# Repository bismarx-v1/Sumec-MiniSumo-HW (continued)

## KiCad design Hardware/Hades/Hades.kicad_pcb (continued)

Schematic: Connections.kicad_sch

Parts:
C68, C69, C70, C71: 100n; C_0402_1005Metric
D2, D3, D4, D5: SD103AWS; D_SOD-323
FB3, FB4, FB5, FB6: Ferrite_Bead_Small; L_0402_1005Metric
GPS_BAT1: Conn_01x02; Molex_PicoBlade_53048-0210_1x02_P1.25mm_Horizontal
JP1, JP2: SolderJumper_2_Open; SolderJumper-2_P1.3mm_Open_RoundedPad1.0x1.5mm
JP4: Jumper_3_Open; SolderJumper-3_P1.3mm_Open_RoundedPad1.0x1.5mm
LED13, LED14: G; LED_0603_1608Metric
R40, R41, R42, R43, R44, R45, R46, R47, R48, R49: 10; R_0402_1005Metric
R50, R51: 0; R_0603_1608Metric
R52, R53, R55, R56: 22; R_0402_1005Metric
R54, R57: 560; R_0402_1005Metric
R58, R59: 560; R_0603_1608Metric
SWD1, SWD2: Conn_02x05_Odd_Even; PinHeader_2x05_P1.27mm_Vertical_SMD
U11, U12: otter:CH330; SSOP-8_3.9x5.05mm_P1.27mm
USB1, USB2, USB3, USB4: USB_B_Micro; USB_Micro-B_Wuerth_629105150521_CircularHoles

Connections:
+3V3: JP4.1 (A), SWD1.1, SWD2.1; also elsewhere on the board
+5V: FB3.1, FB4.1, FB5.1, FB6.1; also elsewhere on the board
GND: C68.1, C69.1, C70.1, C71.1, GPS_BAT1.2, R58.1, R59.1, SWD1.3, SWD1.5, SWD1.9, SWD2.3, SWD2.5, SWD2.9, U11.3, U12.3, USB1.5 (GND), USB1.6 (Shield), USB2.5 (GND), USB2.6 (Shield), USB3.5 (GND), USB3.6 (Shield), USB4.5 (GND), USB4.6 (Shield); also elsewhere on the board
GPIO_A_FCC: R40.2; also elsewhere on the board
GPIO_A_NAVC: R40.1; also elsewhere on the board
GPIO_B_FCC: R41.2; also elsewhere on the board
GPIO_B_NAVC: R41.1; also elsewhere on the board
GPIO_C_FCC: R42.2; also elsewhere on the board
GPIO_C_NAVC: R42.1; also elsewhere on the board
GPIO_D_FCC: R43.2; also elsewhere on the board
GPIO_D_NAVC: R43.1; also elsewhere on the board
GPIO_E_FCC: R44.2; also elsewhere on the board
GPIO_E_NAVC: R44.1; also elsewhere on the board
GPIO_F_FCC: R45.2; also elsewhere on the board
GPIO_F_NAVC: R45.1; also elsewhere on the board
GPIO_G_FCC: R46.2; also elsewhere on the board
GPIO_G_NAVC: R46.1; also elsewhere on the board
GPIO_H_FCC: R47.2; also elsewhere on the board
GPIO_H_NAVC: R47.1; also elsewhere on the board
GPS_BAT_BACKUP: JP4.2 (C); also elsewhere on the board
I2C1_SCL_FCC: R50.2; also elsewhere on the board
I2C1_SDA_FCC: R51.2; also elsewhere on the board
I2C2_SCL_NAVC: R50.1; also elsewhere on the board
I2C2_SDA_NAVC: R51.1; also elsewhere on the board
unnamed: C68.2, D4.2 (A), LED13.2 (A), U11.5, USB3.1 (VBUS)
unnamed: C69.2, U11.8
unnamed: C70.2, D5.2 (A), LED14.2 (A), U12.5, USB4.1 (VBUS)
unnamed: C71.2, U12.8
unnamed: D2.1 (K), FB3.2
unnamed: D2.2 (A), JP1.1 (A), USB1.1 (VBUS)
unnamed: D3.1 (K), FB4.2
unnamed: D3.2 (A), JP2.1 (A), USB2.1 (VBUS)
unnamed: D4.1 (K), FB5.2
unnamed: D5.1 (K), FB6.2
unnamed 119: GPS_BAT1.1, JP4.3 (B); also elsewhere on the board
unnamed: LED13.1 (K), R58.2
unnamed: LED14.1 (K), R59.2
unnamed: R52.2, USB1.3 (D+)
unnamed: R53.2, USB1.2 (D-)
unnamed: R54.2, USB1.4 (ID)
unnamed: R55.2, USB2.3 (D+)
unnamed: R56.2, USB2.2 (D-)
unnamed: R57.2, USB2.4 (ID)
unnamed: U11.1, USB3.3 (D+)
unnamed: U11.2, USB3.2 (D-)
unnamed: U12.1, USB4.3 (D+)
unnamed: U12.2, USB4.2 (D-)
UART1_RX_FCC: U11.6; also elsewhere on the board
UART1_TX_FCC: U11.7; also elsewhere on the board
UART2_RX_FCC: R48.2; also elsewhere on the board
UART2_RX_NAVC: R49.1; also elsewhere on the board
UART2_TX_FCC: R49.2; also elsewhere on the board
UART2_TX_NAVC: R48.1; also elsewhere on the board
UART3_RX_NAVC: U12.6; also elsewhere on the board
UART3_TX_NAVC: U12.7; also elsewhere on the board
USB_DM_FCC: R53.1; also elsewhere on the board
USB_DM_NAVC: R56.1; also elsewhere on the board
USB_DP_FCC: R52.1; also elsewhere on the board
USB_DP_NAVC: R55.1; also elsewhere on the board
USB_ID_FCC: R54.1; also elsewhere on the board
USB_ID_NAVC: R57.1; also elsewhere on the board
USB_VBUS_FCC: JP1.2 (B); also elsewhere on the board
USB_VBUS_NAVC: JP2.2 (B); also elsewhere on the board

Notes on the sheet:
GPS Backup Battery
UART Connections
Connections (FCC <-> NAVC)
USB Debug
I2C Connections
Connector: M50-3600542R
Serial Wire Debug
CH330 UART to USB Converters
USB Programming
GPIO Connections
Connectors (Programming & Debug)
GPS Backup Battery Jumper and Connector

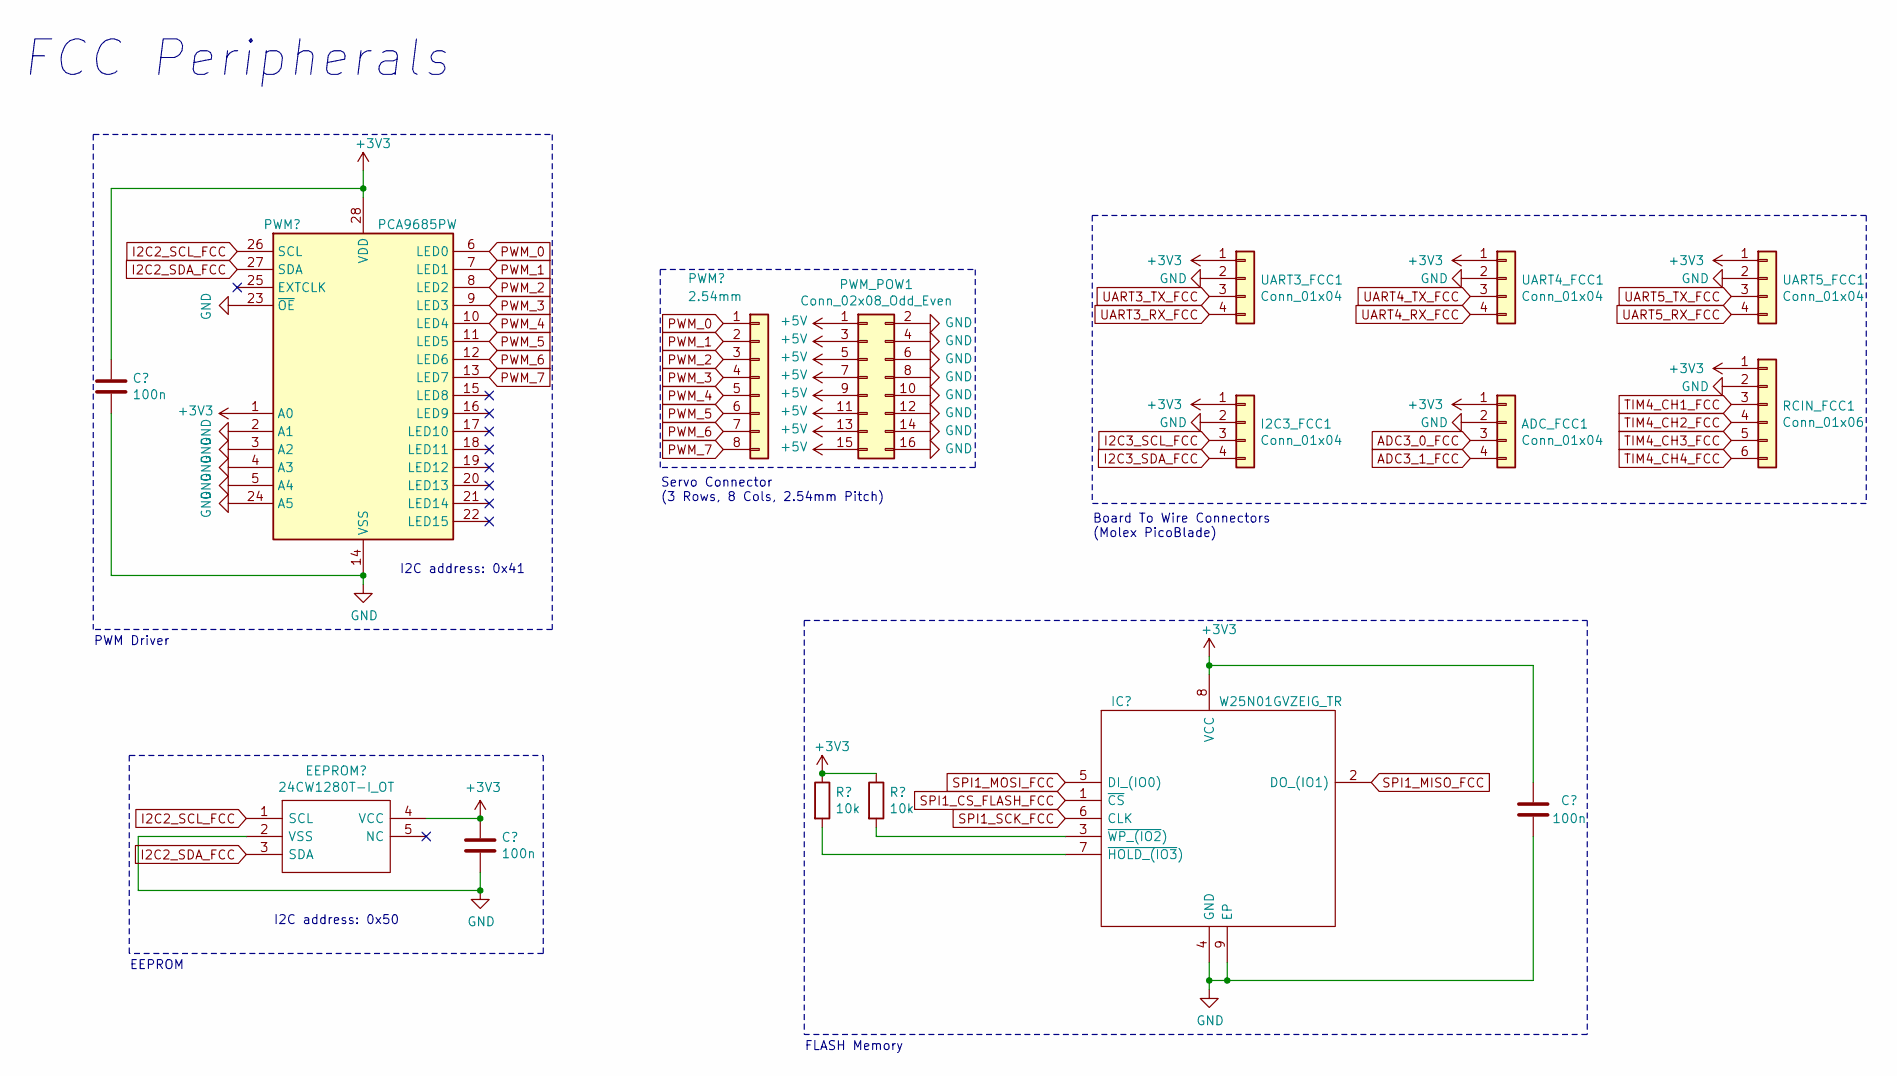
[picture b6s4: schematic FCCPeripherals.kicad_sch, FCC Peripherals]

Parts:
ADC_FCC1: Conn_01x04; Molex_PicoBlade_53048-0410_1x04_P1.25mm_Horizontal
C34, C35, C36: 100n; C_0402_1005Metric
I2C3_FCC1: Conn_01x04; Molex_PicoBlade_53048-0410_1x04_P1.25mm_Horizontal
PWM_POW1: Conn_02x08_Odd_Even; PinHeader_2x08_P2.54mm_Vertical
PWM_SIG1: 2.54mm; PinHeader_1x08_P2.54mm_Vertical
R24, R25: 10k; R_0402_1005Metric
RCIN_FCC1: Conn_01x06; Molex_PicoBlade_53048-0610_1x06_P1.25mm_Horizontal
U2: PCA9685PW; TSSOP-28_4.4x9.7mm_P0.65mm
U3: 24CW1280T-I_OT; SOT95P280X145-5N; Manufacturer_Part_Number 24CW1280T-I/OT; Mouser Part Number 579-24CW1280T-I/OT
U4: W25N01GVZEIG_TR; SON127P800X600X80-9N-D; Manufacturer_Part_Number W25N01GVZEIG TR; Mouser Part Number 454-W25N01GVZEIGTR
UART3_FCC1, UART4_FCC1, UART5_FCC1: Conn_01x04; Molex_PicoBlade_53048-0410_1x04_P1.25mm_Horizontal

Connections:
+3V3: ADC_FCC1.1, C34.1, C35.1, C36.2, I2C3_FCC1.1, R24.1, R25.1, RCIN_FCC1.1, U2.1 (A0), U2.28 (VDD), U3.4 (VCC), U4.8 (VCC), UART3_FCC1.1, UART4_FCC1.1, UART5_FCC1.1; also elsewhere on the board
+5V: PWM_POW1.1, PWM_POW1.3, PWM_POW1.5, PWM_POW1.7, PWM_POW1.9, PWM_POW1.11, PWM_POW1.13, PWM_POW1.15; also elsewhere on the board
GND: ADC_FCC1.2, C34.2, C35.2, C36.1, I2C3_FCC1.2, PWM_POW1.2, PWM_POW1.4, PWM_POW1.6, PWM_POW1.8, PWM_POW1.10, PWM_POW1.12, PWM_POW1.14, PWM_POW1.16, RCIN_FCC1.2, U2.2 (A1), U2.3 (A2), U2.4 (A3), U2.5 (A4), U2.14 (VSS), U2.23 (~OE), U2.24 (A5), U3.2 (VSS), U4.4 (GND), U4.9 (EP), UART3_FCC1.2, UART4_FCC1.2, UART5_FCC1.2; also elsewhere on the board
I2C2_SCL_FCC: U2.26 (SCL), U3.1 (SCL); also elsewhere on the board
I2C2_SDA_FCC: U2.27 (SDA), U3.3 (SDA); also elsewhere on the board
unnamed: R24.2, U4.7 (~HOLD_(IO3))
unnamed: R25.2, U4.3 (~WP_(IO2))
PWM_0: PWM_SIG1.1, U2.6 (LED0)
PWM_1: PWM_SIG1.2, U2.7 (LED1)
PWM_2: PWM_SIG1.3, U2.8 (LED2)
PWM_3: PWM_SIG1.4, U2.9 (LED3)
PWM_4: PWM_SIG1.5, U2.10 (LED4)
PWM_5: PWM_SIG1.6, U2.11 (LED5)
PWM_6: PWM_SIG1.7, U2.12 (LED6)
PWM_7: PWM_SIG1.8, U2.13 (LED7)
SPI1_CS_FLASH_FCC: U4.1 (~CS); also elsewhere on the board
SPI1_MISO_FCC: U4.2 (DO_(IO1)); also elsewhere on the board
SPI1_MOSI_FCC: U4.5 (DI_(IO0)); also elsewhere on the board
SPI1_SCK_FCC: U4.6 (CLK); also elsewhere on the board

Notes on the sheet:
I2C address: 0x50
PWM Driver
Servo Connector (3 Rows, 8 Cols, 2.54mm Pitch)
Board To Wire Connectors (Molex PicoBlade)
I2C address: 0x41
FCC Peripherals
EEPROM
FLASH Memory

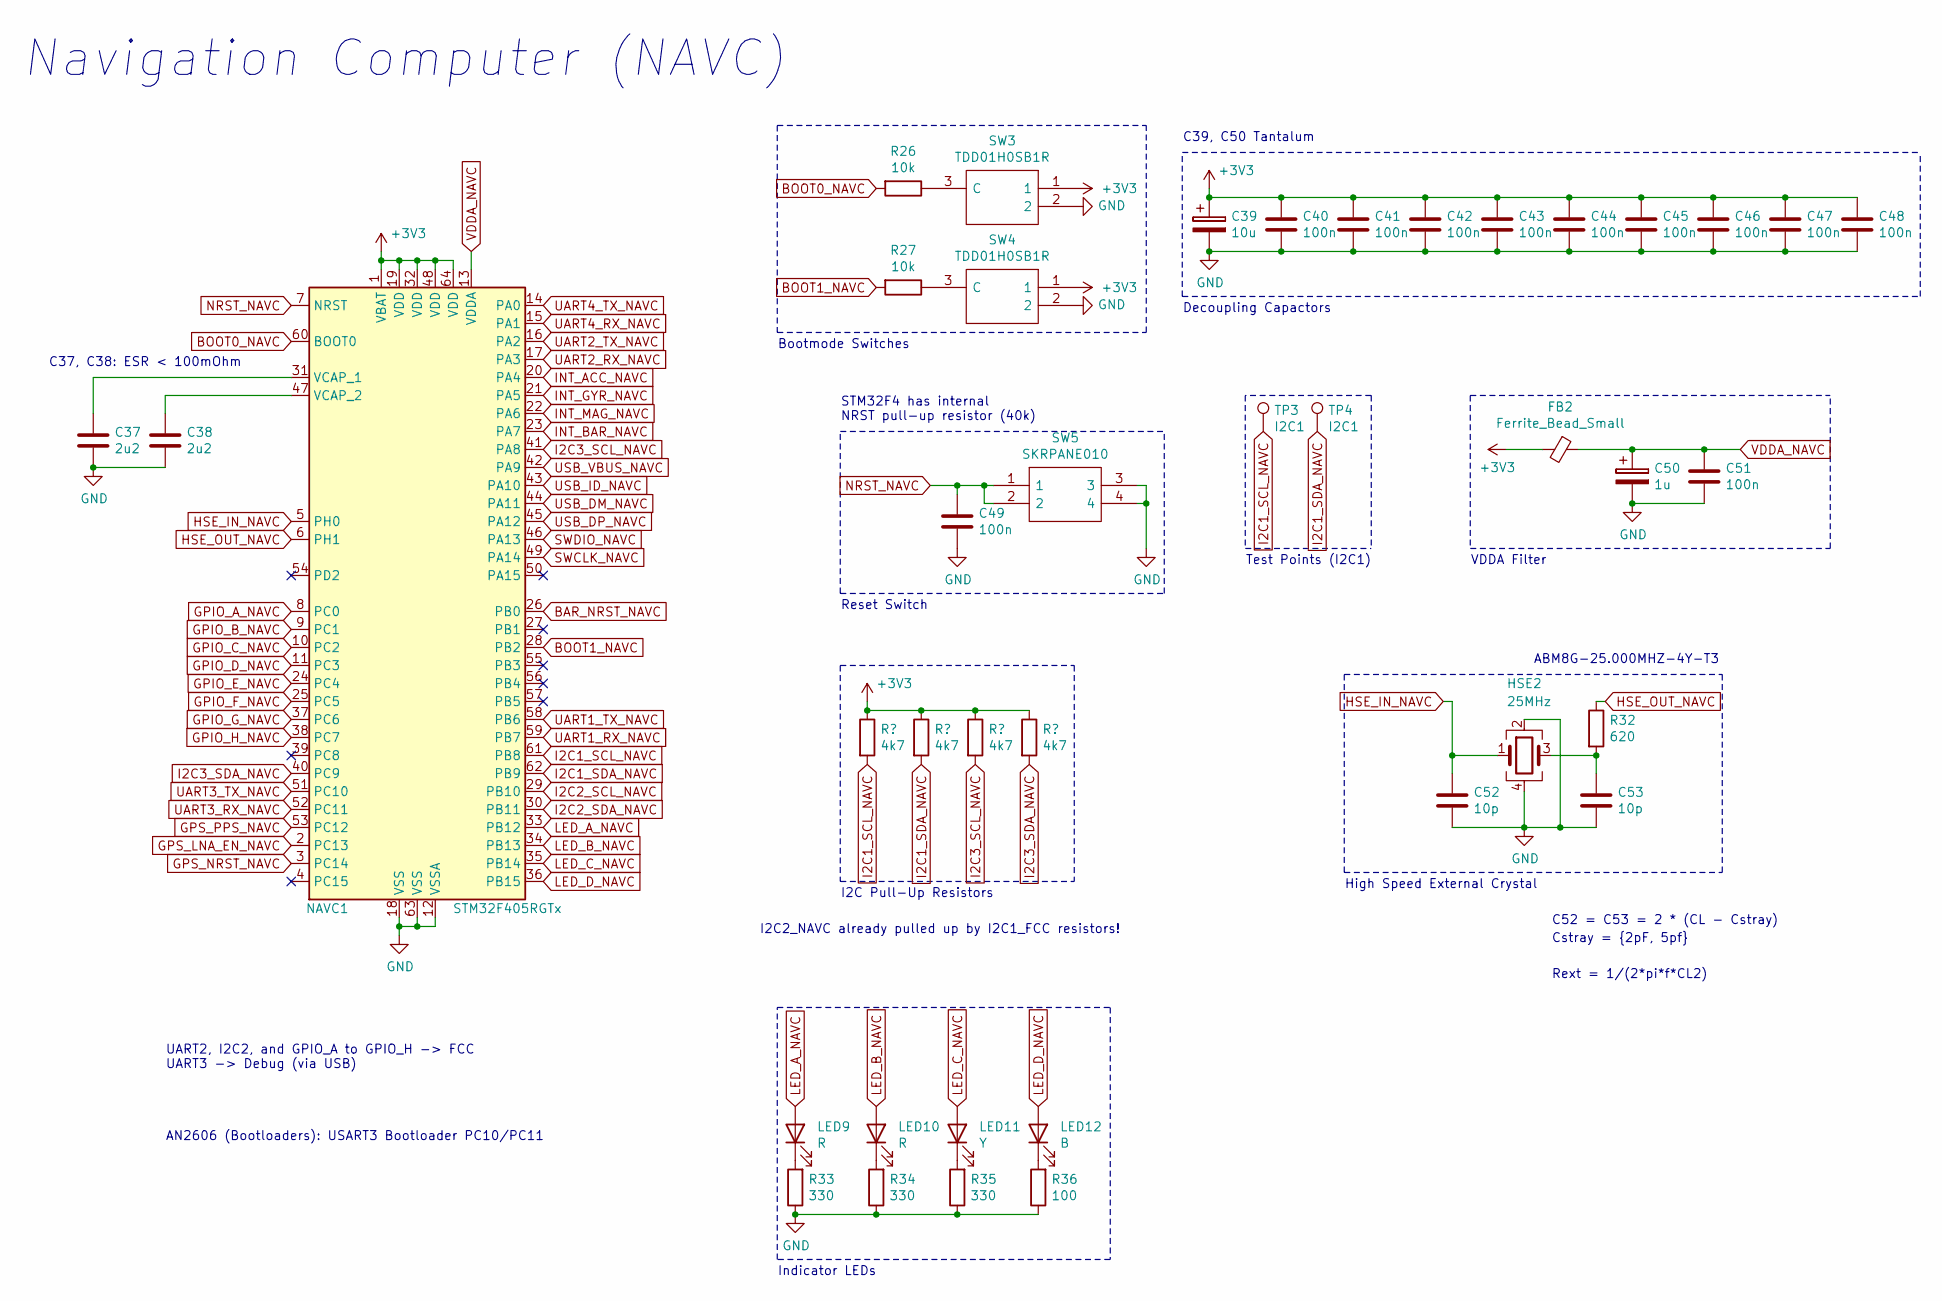
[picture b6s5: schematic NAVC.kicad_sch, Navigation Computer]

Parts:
C37, C38: 2u2; C_0603_1608Metric
C39: 10u; C_0603_1608Metric
C40, C41, C42, C43, C44, C45, C46, C47, C48, C49, C51: 100n; C_0402_1005Metric
C50: 1u; C_0603_1608Metric
C52, C53: 10p; C_0402_1005Metric
FB2: Ferrite_Bead_Small; L_0402_1005Metric
HSE2: 25MHz; Crystal_SMD_Abracon_ABM8G-4Pin_3.2x2.5mm
LED9, LED10: R; LED_0603_1608Metric
LED11: Y; LED_0603_1608Metric
LED12: B; LED_0603_1608Metric
NAVC1: STM32F405RGTx; LQFP-64_10x10mm_P0.5mm
R26, R27: 10k; R_0402_1005Metric
R28, R29, R30, R31: 4k7; R_0402_1005Metric
R32: 620; R_0603_1608Metric
R33, R34, R35: 330; R_0603_1608Metric
R36: 100; R_0603_1608Metric
SW3, SW4: TDD01H0SB1R; SOT175P420X230-3N; Manufacturer_Part_Number TDD01H0SB1R; Mouser Part Number 611-TDD01H0SB1R
SW5: SKRPANE010; SKRPADE010; Manufacturer_Part_Number SKRPANE010; Mouser Part Number 688-SKRPANE010
TP3, TP4: I2C1; TestPoint_Pad_D1.5mm

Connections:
+3V3: C39.1, C40.1, C41.1, C42.1, C43.1, C44.1, C45.1, C46.1, C47.1, C48.1, FB2.2, NAVC1.1 (VBAT), NAVC1.19 (VDD), NAVC1.32 (VDD), NAVC1.48 (VDD), NAVC1.64 (VDD), R28.1, R29.1, R30.1, R31.1, SW3.1, SW4.1; also elsewhere on the board
BOOT0_NAVC: NAVC1.60 (BOOT0), R26.2; also elsewhere on the board
BOOT1_NAVC: NAVC1.28 (PB2), R27.2; also elsewhere on the board
GND: C37.2, C38.2, C39.2, C40.2, C41.2, C42.2, C43.2, C44.2, C45.2, C46.2, C47.2, C48.2, C49.2, C50.2, C51.2, C52.2, C53.2, HSE2.2, HSE2.4, NAVC1.12 (VSSA), NAVC1.18 (VSS), NAVC1.63 (VSS), R33.1, R34.1, R35.1, R36.1, SW3.2, SW4.2, SW5.3, SW5.4; also elsewhere on the board
HSE_IN_NAVC: C52.1, HSE2.1, NAVC1.5 (PH0); also elsewhere on the board
HSE_OUT_NAVC: NAVC1.6 (PH1), R32.1; also elsewhere on the board
I2C1_SCL_NAVC: NAVC1.61 (PB8), R28.2, TP3.1; also elsewhere on the board
I2C1_SDA_NAVC: NAVC1.62 (PB9), R29.2, TP4.1; also elsewhere on the board
I2C3_SCL_NAVC: NAVC1.41 (PA8), R30.2; also elsewhere on the board
I2C3_SDA_NAVC: NAVC1.40 (PC9), R31.2; also elsewhere on the board
LED_A_NAVC: LED9.2 (A), NAVC1.33 (PB12); also elsewhere on the board
LED_B_NAVC: LED10.2 (A), NAVC1.34 (PB13); also elsewhere on the board
LED_C_NAVC: LED11.2 (A), NAVC1.35 (PB14); also elsewhere on the board
LED_D_NAVC: LED12.2 (A), NAVC1.36 (PB15); also elsewhere on the board
NRST_NAVC: C49.1, NAVC1.7 (NRST), SW5.1, SW5.2; also elsewhere on the board
unnamed 68: C37.1, NAVC1.31 (VCAP_1); also elsewhere on the board
unnamed 69: C38.1, NAVC1.47 (VCAP_2); also elsewhere on the board
unnamed: C53.1, HSE2.3, R32.2
unnamed: LED9.1 (K), R33.2
unnamed: LED10.1 (K), R34.2
unnamed: LED11.1 (K), R35.2
unnamed: LED12.1 (K), R36.2
unnamed: R26.1, SW3.3 (C)
unnamed: R27.1, SW4.3 (C)
VDDA_NAVC: C50.1, C51.1, FB2.1, NAVC1.13 (VDDA); also elsewhere on the board

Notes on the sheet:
C39, C50 Tantalum
Decoupling Capactors
I2C2_NAVC already pulled up by I2C1_FCC resistors!
Bootmode Switches
Reset Switch
Test Points (I2C1)
VDDA Filter
I2C Pull-Up Resistors
AN2606 (Bootloaders): USART3 Bootloader PC10/PC11
C37, C38: ESR < 100mOhm
Cstray = {2pF, 5pf}
UART2, I2C2, and GPIO_A to GPIO_H -> FCC UART3 -> Debug (via USB)
ABM8G-25.000MHZ-4Y-T3
High Speed External Crystal
Navigation Computer (NAVC)
Rext = 1/(2*pi*f*CL2)
C52 = C53 = 2 * (CL - Cstray)
Indicator LEDs
STM32F4 has internal NRST pull-up resistor (40k)

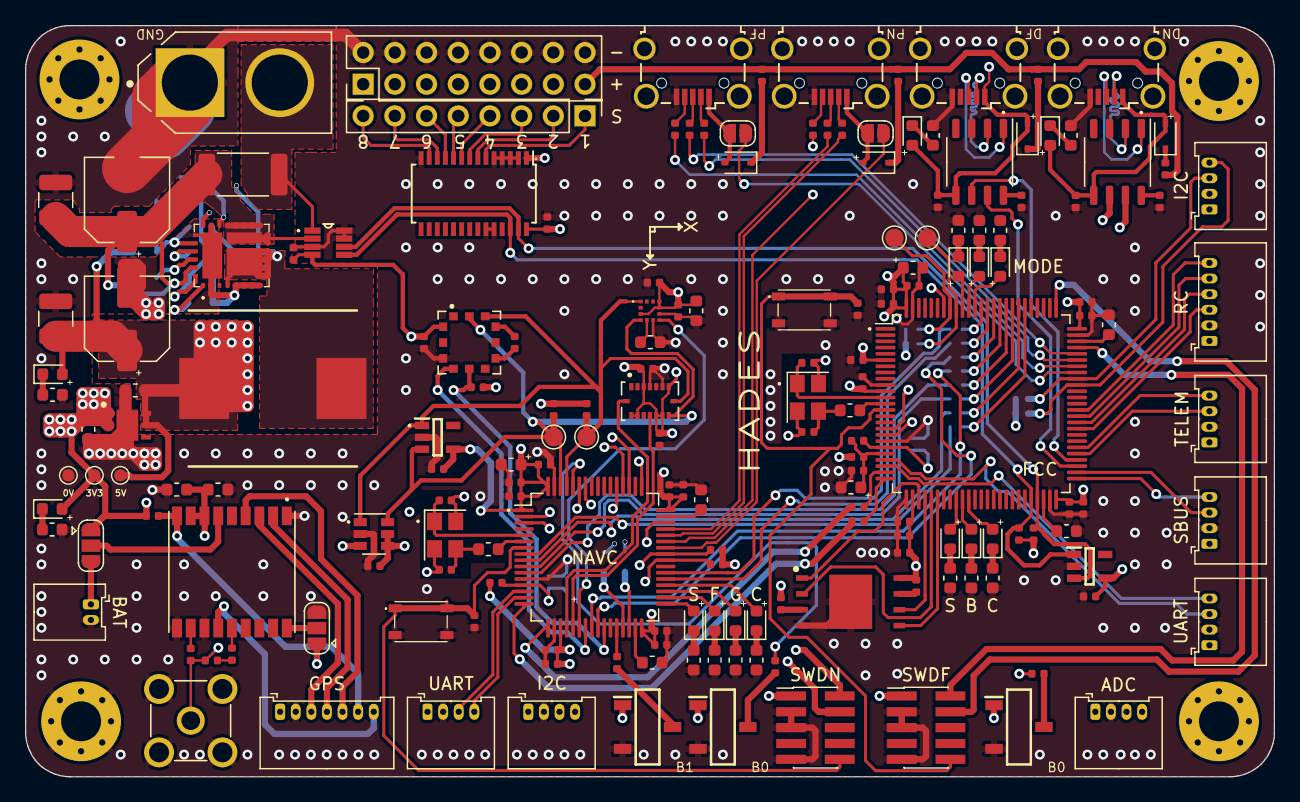
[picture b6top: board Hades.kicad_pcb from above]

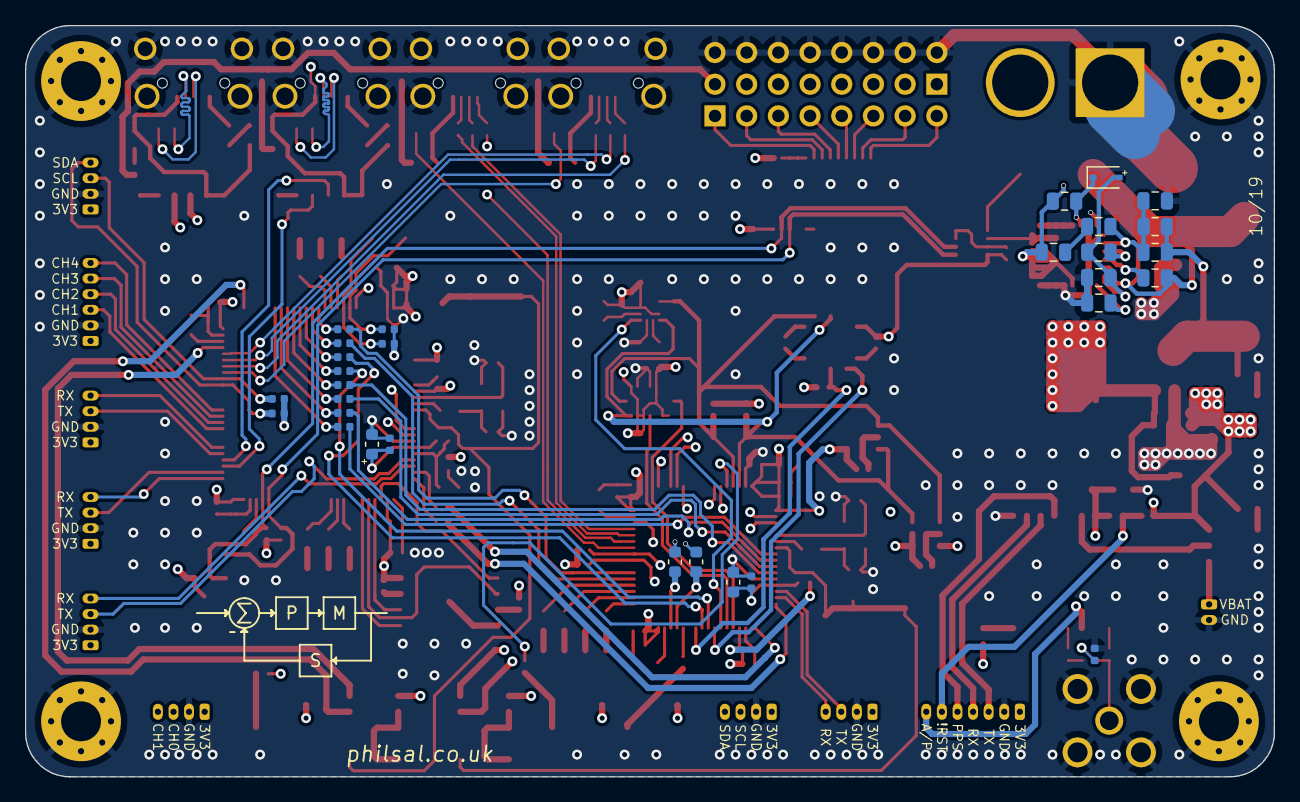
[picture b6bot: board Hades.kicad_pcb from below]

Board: 4 copper layers, 100.1 x 60.2 mm, 211 parts (30 on the bottom side), 174 nets.

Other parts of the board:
5V, 5V#2, 5V#3: TestPoint_Pad_D1.0mm
ADC: Conn_01x04; Molex_PicoBlade_53048-0410_1x04_P1.25mm_Horizontal
BAT: Conn_01x02; Molex_PicoBlade_53048-0210_1x02_P1.25mm_Horizontal
FCC: STM32H753VITx; LQFP-100_14x14mm_P0.5mm
GPS: Conn_01x07; Molex_PicoBlade_53048-0710_1x07_P1.25mm_Horizontal
I2C, I2C#2: Conn_01x04; Molex_PicoBlade_53048-0410_1x04_P1.25mm_Horizontal
NAVC: STM32F405RGTx; LQFP-64_10x10mm_P0.5mm
RC: Conn_01x06; Molex_PicoBlade_53048-0610_1x06_P1.25mm_Horizontal
SBUS: Conn_01x04; Molex_PicoBlade_53048-0410_1x04_P1.25mm_Horizontal
SWDF: Conn_02x05_Odd_Even; PinHeader_2x05_P1.27mm_Vertical_SMD
SWDN: Conn_02x05_Odd_Even; PinHeader_2x05_P1.27mm_Vertical_SMD
TELEM: Conn_01x04; Molex_PicoBlade_53048-0410_1x04_P1.25mm_Horizontal
UART: Conn_01x04; Molex_PicoBlade_53048-0410_1x04_P1.25mm_Horizontal
UART#2: Conn_01x04; Molex_PicoBlade_53048-0410_1x04_P1.25mm_Horizontal

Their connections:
+3V3: 5V#2.1, ADC.1, FCC.6, FCC.11, FCC.27, FCC.50, FCC.75, FCC.100, GPS.1, I2C.1, I2C#2.1, NAVC.1, NAVC.19, NAVC.32, NAVC.48, NAVC.64, RC.1, SBUS.1, SWDF.1, SWDN.1, TELEM.1, UART.1, UART#2.1; also elsewhere on the board
+5V: 5V.1; also elsewhere on the board
ADC3_0_FCC: ADC.3, FCC.17
ADC3_1_FCC: ADC.4, FCC.18
BAR_NRST_NAVC: NAVC.26; also elsewhere on the board
BOOT0_FCC: FCC.94; also elsewhere on the board
BOOT0_NAVC: NAVC.60; also elsewhere on the board
BOOT1_NAVC: NAVC.28; also elsewhere on the board
GND: 5V#3.1, ADC.2, BAT.2, FCC.10, FCC.19, FCC.26, FCC.49, FCC.74, FCC.99, GPS.2, I2C.2, I2C#2.2, NAVC.12, NAVC.18, NAVC.63, RC.2, SBUS.2, SWDF.3, SWDF.5, SWDF.9, SWDN.3, SWDN.5, SWDN.9, TELEM.2, UART.2, UART#2.2; also elsewhere on the board
GPIO_A_FCC: FCC.81; also elsewhere on the board
GPIO_A_NAVC: NAVC.8; also elsewhere on the board
GPIO_B_FCC: FCC.82; also elsewhere on the board
GPIO_B_NAVC: NAVC.9; also elsewhere on the board
GPIO_C_FCC: FCC.83; also elsewhere on the board
GPIO_C_NAVC: NAVC.10; also elsewhere on the board
GPIO_D_FCC: FCC.84; also elsewhere on the board
GPIO_D_NAVC: NAVC.11; also elsewhere on the board
GPIO_E_FCC: FCC.85; also elsewhere on the board
GPIO_E_NAVC: NAVC.24; also elsewhere on the board
GPIO_F_FCC: FCC.86; also elsewhere on the board
GPIO_F_NAVC: NAVC.25; also elsewhere on the board
GPIO_G_FCC: FCC.87; also elsewhere on the board
GPIO_G_NAVC: NAVC.37; also elsewhere on the board
GPIO_H_FCC: FCC.88; also elsewhere on the board
GPIO_H_NAVC: NAVC.38; also elsewhere on the board
GPS_LNA_EN_NAVC: GPS.7, NAVC.2; also elsewhere on the board
GPS_NRST_NAVC: GPS.6, NAVC.3; also elsewhere on the board
GPS_PPS_NAVC: GPS.5, NAVC.53; also elsewhere on the board
HSE_IN_FCC: FCC.12; also elsewhere on the board
HSE_IN_NAVC: NAVC.5; also elsewhere on the board
HSE_OUT_FCC: FCC.13; also elsewhere on the board
HSE_OUT_NAVC: NAVC.6; also elsewhere on the board
I2C1_SCL_FCC: FCC.92; also elsewhere on the board
I2C1_SCL_NAVC: NAVC.61; also elsewhere on the board
I2C1_SDA_FCC: FCC.93; also elsewhere on the board
I2C1_SDA_NAVC: NAVC.62; also elsewhere on the board
I2C2_SCL_FCC: FCC.46; also elsewhere on the board
I2C2_SCL_NAVC: NAVC.29; also elsewhere on the board
I2C2_SDA_FCC: FCC.47; also elsewhere on the board
I2C2_SDA_NAVC: NAVC.30; also elsewhere on the board
I2C3_SCL_FCC: FCC.67, I2C.3; also elsewhere on the board
I2C3_SCL_NAVC: I2C#2.3, NAVC.41; also elsewhere on the board
I2C3_SDA_FCC: FCC.66, I2C.4; also elsewhere on the board
I2C3_SDA_NAVC: I2C#2.4, NAVC.40; also elsewhere on the board
INT_ACC_NAVC: NAVC.20; also elsewhere on the board
INT_BAR_NAVC: NAVC.23; also elsewhere on the board
INT_GYR_NAVC: NAVC.21; also elsewhere on the board
INT_MAG_NAVC: NAVC.22; also elsewhere on the board
LED_A_FCC: FCC.34; also elsewhere on the board
LED_A_NAVC: NAVC.33; also elsewhere on the board
LED_B_FCC: FCC.35; also elsewhere on the board
LED_B_NAVC: NAVC.34; also elsewhere on the board
LED_C_FCC: FCC.36; also elsewhere on the board
LED_C_NAVC: NAVC.35; also elsewhere on the board
LED_D_FCC: FCC.89; also elsewhere on the board
LED_D_NAVC: NAVC.36; also elsewhere on the board
LED_E_FCC: FCC.90; also elsewhere on the board
LED_F_FCC: FCC.91; also elsewhere on the board
NRST_FCC: FCC.14, SWDF.10; also elsewhere on the board
NRST_NAVC: NAVC.7, SWDN.10; also elsewhere on the board
unnamed 65: FCC.48; also elsewhere on the board
unnamed 66: FCC.73; also elsewhere on the board
unnamed 68: NAVC.31; also elsewhere on the board
unnamed 69: NAVC.47; also elsewhere on the board
unnamed 119: BAT.1; also elsewhere on the board
SPI1_CS_FLASH_FCC: FCC.28; also elsewhere on the board
SPI1_MISO_FCC: FCC.30; also elsewhere on the board
SPI1_MOSI_FCC: FCC.31; also elsewhere on the board
SPI1_SCK_FCC: FCC.29; also elsewhere on the board
SWCLK_FCC: FCC.76, SWDF.4
SWCLK_NAVC: NAVC.49, SWDN.4
SWDIO_FCC: FCC.72, SWDF.2
SWDIO_NAVC: NAVC.46, SWDN.2
TIM4_CH1_FCC: FCC.59, RC.3
TIM4_CH2_FCC: FCC.60, RC.4
TIM4_CH3_FCC: FCC.61, RC.5
TIM4_CH4_FCC: FCC.62, RC.6
UART1_RX_FCC: FCC.54; also elsewhere on the board
UART1_RX_NAVC: GPS.4, NAVC.59; also elsewhere on the board
UART1_TX_FCC: FCC.53; also elsewhere on the board
UART1_TX_NAVC: GPS.3, NAVC.58; also elsewhere on the board
UART2_RX_FCC: FCC.25; also elsewhere on the board
UART2_RX_NAVC: NAVC.17; also elsewhere on the board
UART2_TX_FCC: FCC.24; also elsewhere on the board
UART2_TX_NAVC: NAVC.16; also elsewhere on the board
UART3_RX_FCC: FCC.56, TELEM.4
UART3_RX_NAVC: NAVC.52; also elsewhere on the board
UART3_TX_FCC: FCC.55, TELEM.3
UART3_TX_NAVC: NAVC.51; also elsewhere on the board
UART4_RX_FCC: FCC.23, UART#2.4
UART4_RX_NAVC: NAVC.15, UART.4
UART4_TX_FCC: FCC.22, UART#2.3
UART4_TX_NAVC: NAVC.14, UART.3
UART5_RX_FCC: FCC.51, SBUS.4
UART5_TX_FCC: FCC.52, SBUS.3
USB_DM_FCC: FCC.70; also elsewhere on the board
USB_DM_NAVC: NAVC.44; also elsewhere on the board
USB_DP_FCC: FCC.71; also elsewhere on the board
USB_DP_NAVC: NAVC.45; also elsewhere on the board
USB_ID_FCC: FCC.69; also elsewhere on the board
USB_ID_NAVC: NAVC.43; also elsewhere on the board
USB_VBUS_FCC: FCC.68; also elsewhere on the board
USB_VBUS_NAVC: NAVC.42; also elsewhere on the board
VDDA_FCC: FCC.21; also elsewhere on the board
VDDA_NAVC: NAVC.13; also elsewhere on the board
VREF+_FCC: FCC.20; also elsewhere on the board

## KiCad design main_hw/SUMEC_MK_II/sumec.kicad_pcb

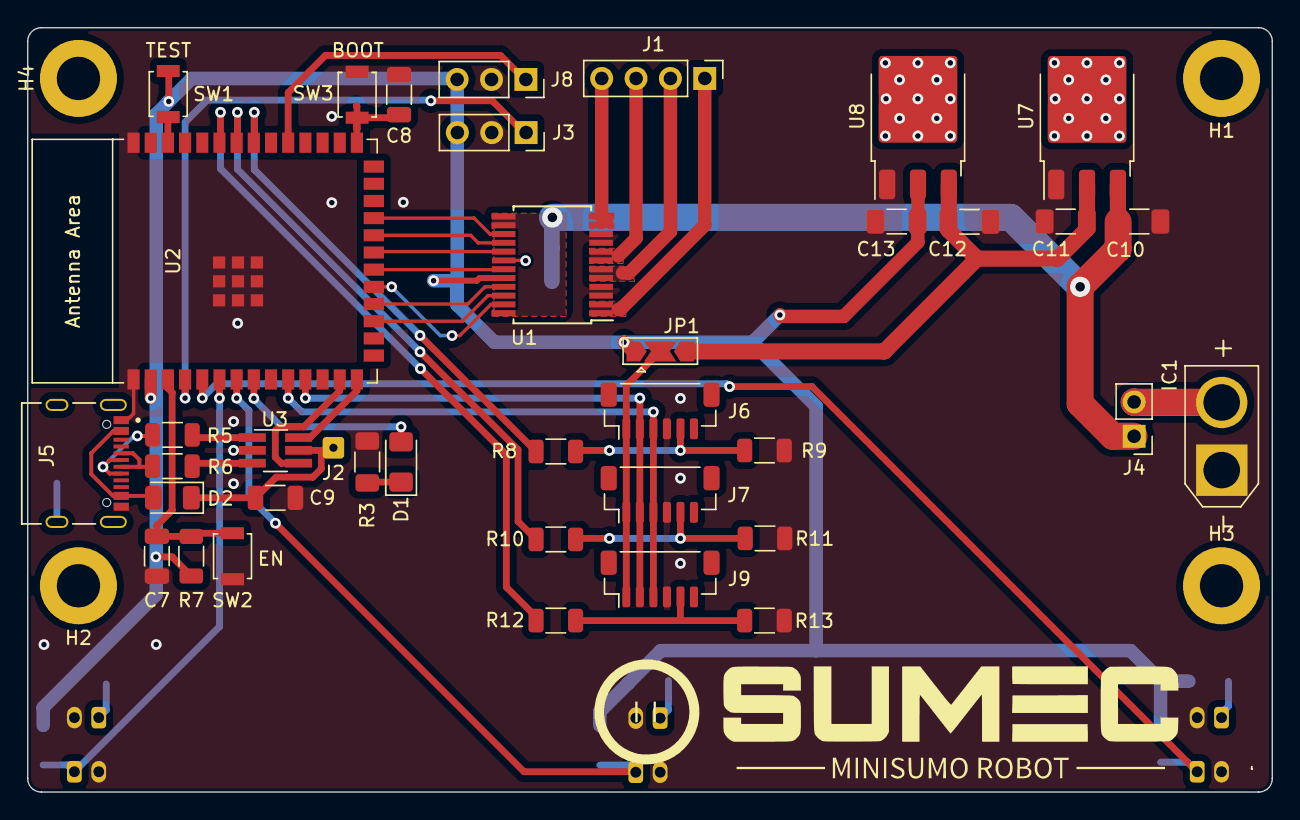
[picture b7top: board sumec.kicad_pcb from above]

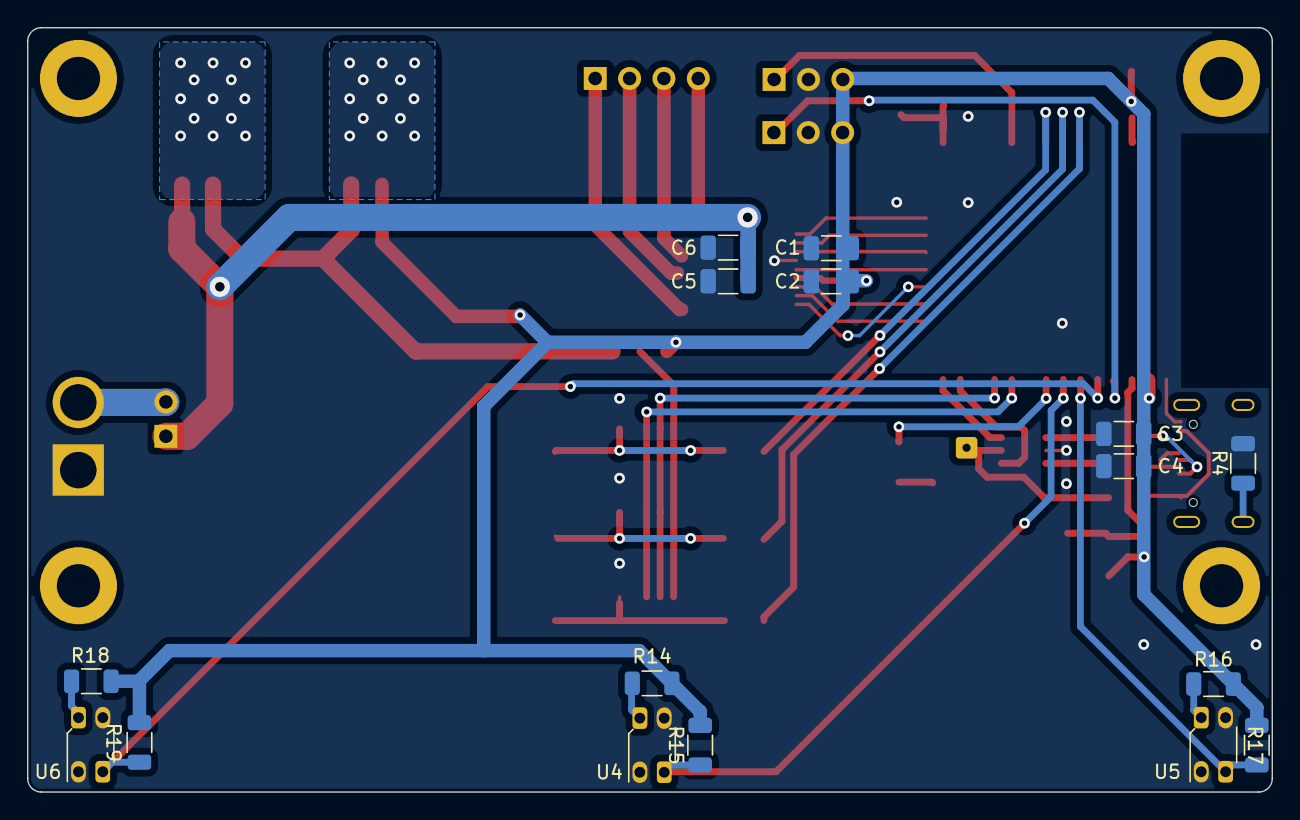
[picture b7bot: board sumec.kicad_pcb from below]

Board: 2 copper layers, 92.0 x 56.5 mm, 59 parts (16 on the bottom side), 47 nets.

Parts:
C1: 10uF.hb; C_1206_3216Metric
C2: 1uF.hb; C_1206_3216Metric
C3: 10uF.mcu; C_1206_3216Metric
C4: 100nF.mcu; C_1206_3216Metric
C5: 10uF.hbc; C_1206_3216Metric
C6: 100nF.hbc; C_1206_3216Metric
C7: 100nF.en; C_1206_3216Metric
C8: 100nF.boot; C_1206_3216Metric
C9: 100nF; C_1206_3216Metric
C10, C11, C12, C13: 10uF.stabl; C_1206_3216Metric_Pad1.33x1.80mm_HandSolder
D1: LED; LED_1206_3216Metric_Pad1.42x1.75mm_HandSolder
D2: 1N5819; D_1206_3216Metric
H1, H2, H3, H4: MountingHole M3; MountingHole_3.2mm_M3_ISO7380_Pad
IC1: XT30U-F; AMASS_XT30U-M_1x02_P5.0mm_Vertical
J1: Conn_01x04_Pin; PinHeader_1x04_P2.54mm_Vertical
J2: Conn_01x01_Pin; SolderWire-0.1sqmm_1x01_D0.4mm_OD1mm
J3: Conn_01x03_Pin; PinSocket_1x03_P2.54mm_Vertical
J4: Conn_01x02; PinHeader_1x02_P2.54mm_Vertical
J5: TYPE-C-31-M-12; HRO_TYPE-C-31-M-12
J6, J7, J9: Conn_01x06_Pin; JST_SH_BM06B-SRSS-TB_1x06-1MP_P1.00mm_Vertical
J8: TSOP382xx; PinSocket_1x03_P2.54mm_Vertical
JP1: SolderJumper_3_Open; SolderJumper-3_P2.0mm_Open_TrianglePad1.0x1.5mm
R1: R; logo even smaller
R3: 220; R_1206_3216Metric_Pad1.30x1.75mm_HandSolder
R4, R8, R9, R10, R11, R12, R13: 0R; R_1206_3216Metric
R5, R6: 15R; R_1206_3216Metric
R7: 10k.mcu; R_1206_3216Metric
R14, R16, R18: 100; R_1206_3216Metric
R15, R17, R19: 10k; R_1206_3216Metric
SW1, SW2, SW3: SW_Push; SW_SPST_B3U-1000P
U1: TB6612FNG; SSOP-24_5.3x8.2mm_P0.65mm
U2: ESP32-S3-WROOM-1
U3: USBLC6-2SC6; TSOT-23-6_HandSoldering
U4, U5, U6: QRE1113; OnSemi_CASE100AQ - QRE1113
U7: LM1084IS-5.0/NOPB; TO-252-3_TabPin2
U8: LM1084IS-3.3/NOPB; TO-252-3_TabPin2

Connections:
+3V3: C1.1, C2.1, C3.1, C4.1, C13.1, J3.3, J8.3 (Vs), JP1.1 (A), R7.2, R14.2, R15.1, R16.2, R17.1, R18.2, R19.1, SW1.1, U1.20 (VCC), U2.2 (3V3), U8.2 (VO)
+5V: C11.1, C12.1, JP1.3 (B), U7.2 (VO), U8.3 (VI)
+8V: C5.1, C6.1, C10.1, J4.1, U1.13 (VM2), U1.14 (VM3), U1.24 (VM1), U7.3 (VI)
AI1: U1.21 (AIN1), U2.18 (GPIO10/TOUCH10/ADC1_CH9/FSPICS0/FSPIIO4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)
AI2: U1.22 (AIN2), U2.17 (GPIO9/TOUCH9/ADC1_CH8/FSPIHD/SUBSPIHD)
BI1: U1.17 (BIN1), U2.21 (GPIO13/TOUCH13/ADC2_CH2/FSPIQ/FSPIIO7/S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)
BI2: U1.16 (BIN2), U2.22 (GPIO14/TOUCH14/ADC2_CH3/FSPIWP/FSPIDQS/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)
BOOT: C8.1, SW3.2, U2.27 (GPIO0/BOOT)
D+: U2.14 (GPIO20/U1CTS/ADC2_CH9/CLK_OUT1/USB_D+), U3.6
D+ IN: J5.A6 (DP1), J5.B6 (DP2), R5.1
D-: U2.13 (GPIO19/U1RTS/ADC2_CH8/CLK_OUT2/USB_D-), U3.4
D- IN: J5.A7 (DN1), J5.B7 (DN2), R6.1
EN: C7.1, R7.1, SW2.2, U2.3 (EN)
GND: C1.2, C2.2, C3.2, C4.2, C5.2, C6.2, C7.2, C8.2, C9.2, C10.2, C11.2, C12.2, C13.2, IC1.1, J3.2, J5.A1_B12 (GND), J5.B1_A12 (GND), J6.4, J7.4, J8.2 (GND), J9.4, R3.2, R4.2, R9.1, R11.1, R13.1, SW2.1, SW3.1, U1.3 (PGND1), U1.4 (PGND1), U1.9 (PGND2), U1.10 (PGND2), U1.18 (GND), U2.1 (GND), U2.40 (GND), U2.41 (GND), U3.2, U4.2 (K), U4.4, U5.2 (K), U5.4, U6.2 (K), U6.4, U7.1 (GND), U8.1 (GND)
IR MODULE: J8.1 (OUT), U2.31 (GPIO38/FSPIWP/SUBSPIWP)
LED: D1.2 (A), U2.8 (GPIO15/U0RTS/ADC2_CH4/XTAL_32K_P)
MOTOR 1 +: J1.1, U1.1 (AO1), U1.2 (AO1)
MOTOR 1 -: J1.2, U1.5 (AO2), U1.6 (AO2)
MOTOR 2 +: J1.4, U1.11 (BO1), U1.12 (BO1)
MOTOR 2 -: J1.3, U1.7 (BO2), U1.8 (BO2)
unnamed: D1.1 (K), R3.1
unnamed: D2.2 (A), J5.A4_B9 (VBUS), J5.B4_A9 (VBUS)
unnamed: J5.S1 (SHIELD), J5.S2 (SHIELD), J5.S3 (SHIELD), J5.S4 (SHIELD), R4.1
unnamed: J6.5, R8.1, R9.2
unnamed: J7.5, R10.1, R11.2
unnamed: J9.5, R12.1, R13.2
unnamed: R5.2, U3.1
unnamed: R6.2, U3.3
unnamed: R14.1, U4.1 (A)
unnamed: R16.1, U5.1 (A)
unnamed: R18.1, U6.1 (A)
PWMA: U1.23 (PWMA), U2.19 (GPIO11/TOUCH11/ADC2_CH0/FSPID/FSPIIO5/S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)
PWMB: U1.15 (PWMB), U2.23 (GPIO21)
QRE1113 A: J3.1, U2.4 (GPIO4/TOUCH4/ADC1_CH3)
QRE1113 B: R15.2, U2.7 (GPIO7/TOUCH7/ADC1_CH6), U4.3
QRE1113 C: R17.2, U2.6 (GPIO6/TOUCH6/ADC1_CH5), U5.3
QRE1113 D: R19.2, U2.5 (GPIO5/TOUCH5/ADC1_CH4), U6.3
SCL: J6.3, J7.3, J9.3, U2.10 (GPIO17/U1TXD/ADC2_CH6)
SDA: J6.2, J7.2, J9.2, U2.11 (GPIO18/U1RXD/ADC2_CH7/CLK_OUT3)
SENSOR_SUPPLY: J6.1, J7.1, J9.1, JP1.2 (C)
STBY: U1.19 (STBY), U2.20 (GPIO12/TOUCH12/ADC2_CH1/FSPICLK/FSPIIO6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)
TEST PROGRAM: SW1.2, U2.38 (GPIO2/TOUCH2/ADC1_CH1)
VBATT: IC1.2, J4.2
VBUS 5V: C9.1, D2.1 (K), J2.1, U3.5
X-SHUT1: R8.2, U2.33 (MTDO/GPIO40/CLK_OUT2)
X-SHUT2: R10.2, U2.34 (MTDI/GPIO41/CLK_OUT1)
X-SHUT3: R12.2, U2.35 (MTMS/GPIO42)

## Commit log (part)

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2025-02-19 PCB repo setup
2025-02-20 Schematic update
2025-02-21 HADES PCB Inspiration - just a file transfer
2025-02-21 HadesMicro and other PCBs with IMUs
2025-02-22 renaming
2025-02-22 Force push
2025-02-24 MK V Schematic update
2025-02-27 Schematic update - finalized
2025-03-03 minor schematic update
2025-03-03 PCB update MKV
2025-03-04 ughhhhhhhh
2025-03-04 minor pcb update
2025-03-04 PCB Updtae MK5
2025-03-05 PCB and 3d update
2025-03-05 PCB update - layout
2025-03-06 pcb routing
2025-03-06 routing update
2025-03-08 PCB pours update
2025-03-08 PCB Update, signal routing
2025-03-14 new step file
2025-03-17 pcb update
2025-03-19 PCB routing update
2025-03-23 a lot of routing and layout updates
2025-03-25 sumec pcb update
2025-03-27 deletion of useless stuff
2025-03-28 SUMEC MKIV
2025-03-30 silkscreen update
2025-03-31 new qre board
2025-03-31 silkscreen
2025-03-31 plotting + boms
2025-04-05 not sure what the update was but ill push it anywat bc ermm idk
2025-04-12 im gonna clean up this later
2025-04-15 gotta push it to the notebook
2025-04-16 67yfhtgftu
2025-04-24 MK5 bugfix fixed POL_L, minor changes, deleted nSLEEP and nFault connections to the MCU
2025-04-25 old things, but its better to have them
2025-04-26 old versions
2025-04-28 MK5 changes and deletion of useless files
2025-05-15 schematic fixes
2025-05-21 Bom stuff
2025-07-12 not suer
2025-08-12 footprint edit
2025-08-26 added art
2025-12-09 edits are needed
2026-01-23 line thickness in PCB editor test
2026-03-01 updates to mk5
2026-03-13 MK5 PCB rework
2026-03-31 MK5 new update of the PCB
2026-03-31 KiNotes update
2026-04-07 silkscreen update and PCB plot
2026-04-10 new MK5.5 update
2026-04-10 rename of mk5.1 version, renamed to mk5 pro
2026-04-11 Rename schematic project to SUMEC_MK_V_Pro
    Update main_hw/SUMEC_MK_V_Pro/SUMEC_MK_V_Pro.kicad_sch: replace project references from "SUMEC_MK_V" to "SUMEC_MK_V_Pro" across many instances so component references match the renamed project. This 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
2026-04-11 Update KiCad PCB render_cache polygons
    Added missing paths: 3V3 for JP3, GND for C1. Minor path optimization was provided.
2026-04-11 Rename sheet reference to SUMEC_MK_V_Pro
    Update the KiCad project file to reference the Pro schematic sheet: changed the sheets entry from "SUMEC_MK_V" to "SUMEC_MK_V_Pro" in SUMEC_MK_V_Pro.kicad_pro to keep the project configuration consis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
2026-04-12 Update SUMEC_MK_V_Pro.kicad_pcb
    Paths redesign: Net-(JP3-A), Net-(U7-RESET), 3V3 and 12V on In2 layer,
2026-04-12 Update SUMEC_MK_V_Pro.kicad_sch
    Added description for PS1 and PS0 pins of BN055 IMU onboard sensor.
2026-04-12 Update SUMEC_MK_V_Pro.kicad_sch
    Added description for COM3 pin of BN055 for I2C address selection.
2026-04-12 Update .gitignore for IDE and KiCad files
    Add common IDE/editor directories (.history, .vscode) and KiCad temporary/lock patterns (*.lck, *-save.kicad_sch) to reduce repo clutter. Update comments to clarify sections and add OldVersions/ to i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
2026-04-13 Bom update
2026-04-13 Brought unchanged MK5 back
    Brought the deleted MK5 back
2026-04-13 SUMEC Mk5 Pro bom update
2026-04-15 Bom update and cleanup
2026-04-27 Final update for MK Pro
    PCB, schematic update, IMU software
2026-05-06 Prepare for release
